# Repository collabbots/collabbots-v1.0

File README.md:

# collabbots-v1.0

Pictures of the setup (July 2019):

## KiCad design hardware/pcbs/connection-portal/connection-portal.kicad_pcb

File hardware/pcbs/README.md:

**Lessons learned**

Possible improvements for v2.0/v1.0 Rev B of the pcbs:

1. Reverse voltage protection using power PMOS, [zener, resistor (and LED for indication)]. **(vv important)**
2. integration of PCA9685 circuit into the pcb itself: reduce form factor and external wiring. **(vv important)**
3. For the connection portal pcb: the interrupt wires have to currently be all powered through one I-High and GND port. Rather have an array of 3 jumpers: interrupt, power, GND so that it is easier to wire and manage micro/limit switches. **(important)**
4. Use bigger (appropriately sized) vias -- comparable to the track thickness
5. Make the LED circuits brighter -- use transistors
6. Make an enclosure for the pcbs, with place for the knobs to come out.
7. Properly label all connections and components on the pcb (both sides for clarity and ease of use)
8. The number of motors is 4, but the connection portal and controller have capacity and connections for 5. This is a mismatch; keep the limit of motors to 4 if the arm design remains the same.
9. Have a port for the switch, which will interrupt the input power. This can be done by having a mount for a fuse between the switch and input power, so that traces don't have to be very thick and instead GND can go through the fuse from the switch. **(vv important)**
10. Have a dedicated place to mount the buck converter output fuse on the controller which could be a thick screw terminal, maybe. **(important)** 
11. The V+ and GND plates act like a capacitor and is dangerous for sensitive equipment or devices monitoring V+ since even after cutting the supply, V+ is floating at 1.5V or higher. Design circuitry to discharge this without overloading the supply and overheating when switched on. **(important)**
12. Arrange the terminal block for the two arms so that it is easier to wire them. one on left and the other on right.
13. Can mount the RPi on the bottom, thereby reducing the PCB footprint by a lot, and also allowing enough space for routing cables for the RPi.
14. Try using SMD components to further reduce the footprint.
15. Can have LED indicators for all the wires for visual debugging and also. Use the on-board 5V supply for that.
16. Try redesigning the pcb such that the design is completely modular. Another controller pcb can add two more arms at maximum. Therefore removing RPi from the board and having it has an optional mount is one step towards achieving this. **(vvv important)**
17. Servo zero set correction circuitry (try adding large capacitors on the output -- make sure to avoid high current surges). **(vv important)**
18. The connection portal will not be necessary if we handle each robot using a small microcontroller. This will also enable parallel control. So, just a USB cable and power supply goes into the robot -- also reduces wiring tremendously.
19. There can be a USB interface board that handles distributing serial commands to multiple robots. So, from a single USB port of the RPi/computer, you have a command handler PCB connected to multiple robots through USB ports. This will promote expandibility of the system.

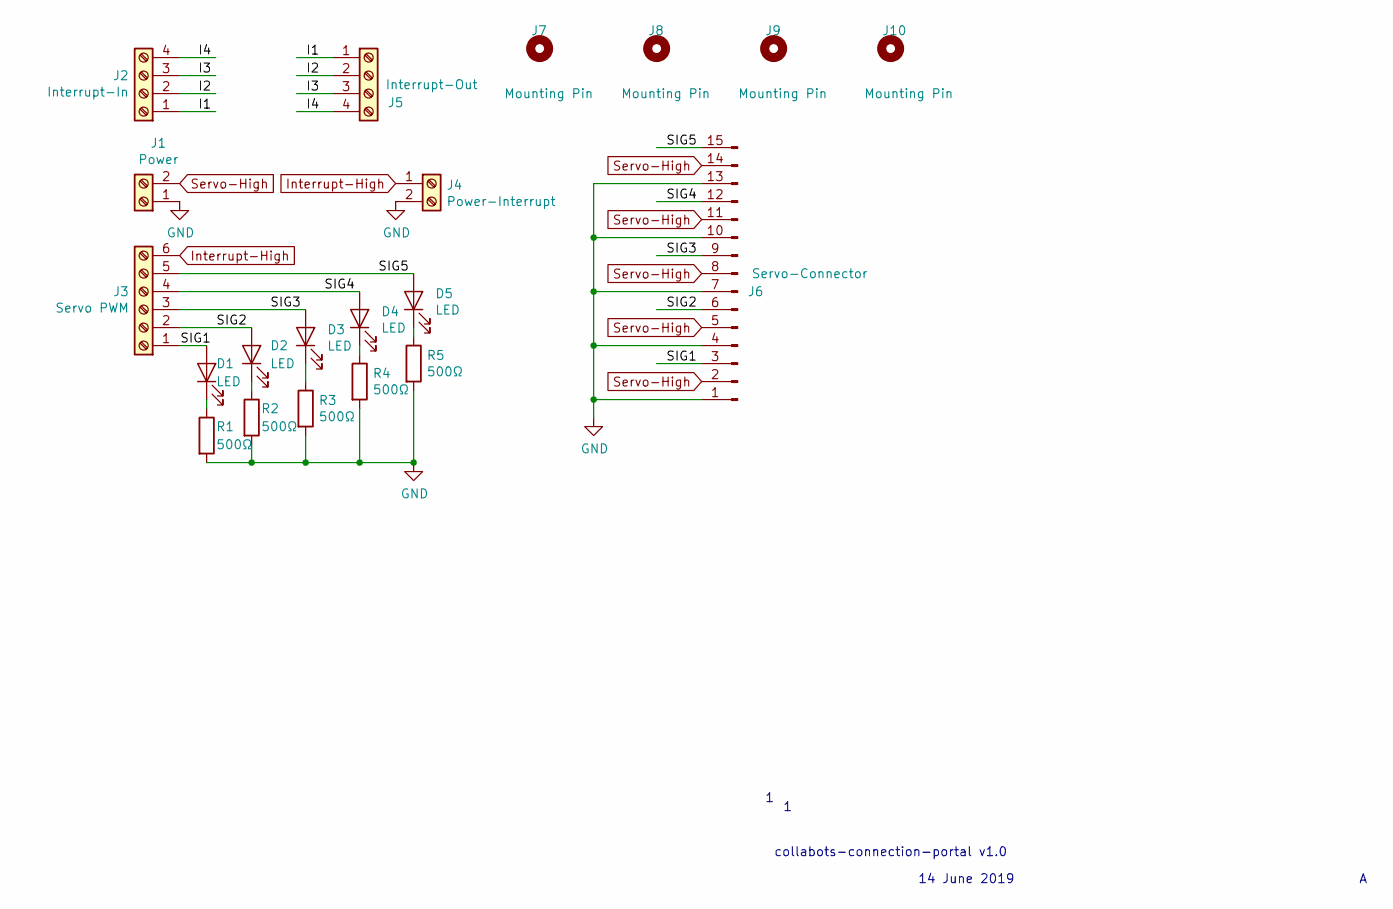
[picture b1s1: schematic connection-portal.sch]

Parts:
D1, D2, D3, D4, D5: LED; LED_Rectangular_W3.9mm_H1.8mm_FlatTop
J1: Power; TerminalBlock_MetzConnect_Type011_RT05502HBWC_1x02_P5.00mm_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
J2: Interrupt-In; TerminalBlock_MetzConnect_Type011_RT05504HBWC_1x04_P5.00mm_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
J3: Servo PWM; TerminalBlock_MetzConnect_Type011_RT05506HBWC_1x06_P5.00mm_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
J4: Power-Interrupt; TerminalBlock_MetzConnect_Type011_RT05502HBWC_1x02_P5.00mm_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
J5: Interrupt-Out; TerminalBlock_MetzConnect_Type011_RT05504HBWC_1x04_P5.00mm_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
J6: Servo-Connector; PinHeader_1x15_P2.54mm_Horizontal
J7, J8, J9, J10: Mounting Pin; MountingHole_3.2mm_M3
R1, R2, R3, R4, R5: 500Ω; R_Axial_DIN0207_L6.3mm_D2.5mm_P10.16mm_Horizontal

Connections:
/I1: J2.1, J5.1
/I2: J2.2, J5.2
/I3: J2.3, J5.3
/I4: J2.4, J5.4
/SIG1: D1.2 (A), J3.1, J6.3
/SIG2: D2.2 (A), J3.2, J6.6
/SIG3: D3.2 (A), J3.3, J6.9
/SIG4: D4.2 (A), J3.4, J6.12
/SIG5: D5.2 (A), J3.5, J6.15
GND: J1.1, J4.2, J6.1, J6.4, J6.7, J6.10, J6.13, R1.2, R2.2, R3.2, R4.2, R5.2
Interrupt-High: J3.6, J4.1
unnamed: D1.1 (K), R1.1
unnamed: D2.1 (K), R2.1
unnamed: D3.1 (K), R3.1
unnamed: D4.1 (K), R4.1
unnamed: D5.1 (K), R5.1
Servo-High: J1.2, J6.2, J6.5, J6.8, J6.11, J6.14

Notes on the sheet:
collabots-connection-portal v1.0
14 June 2019

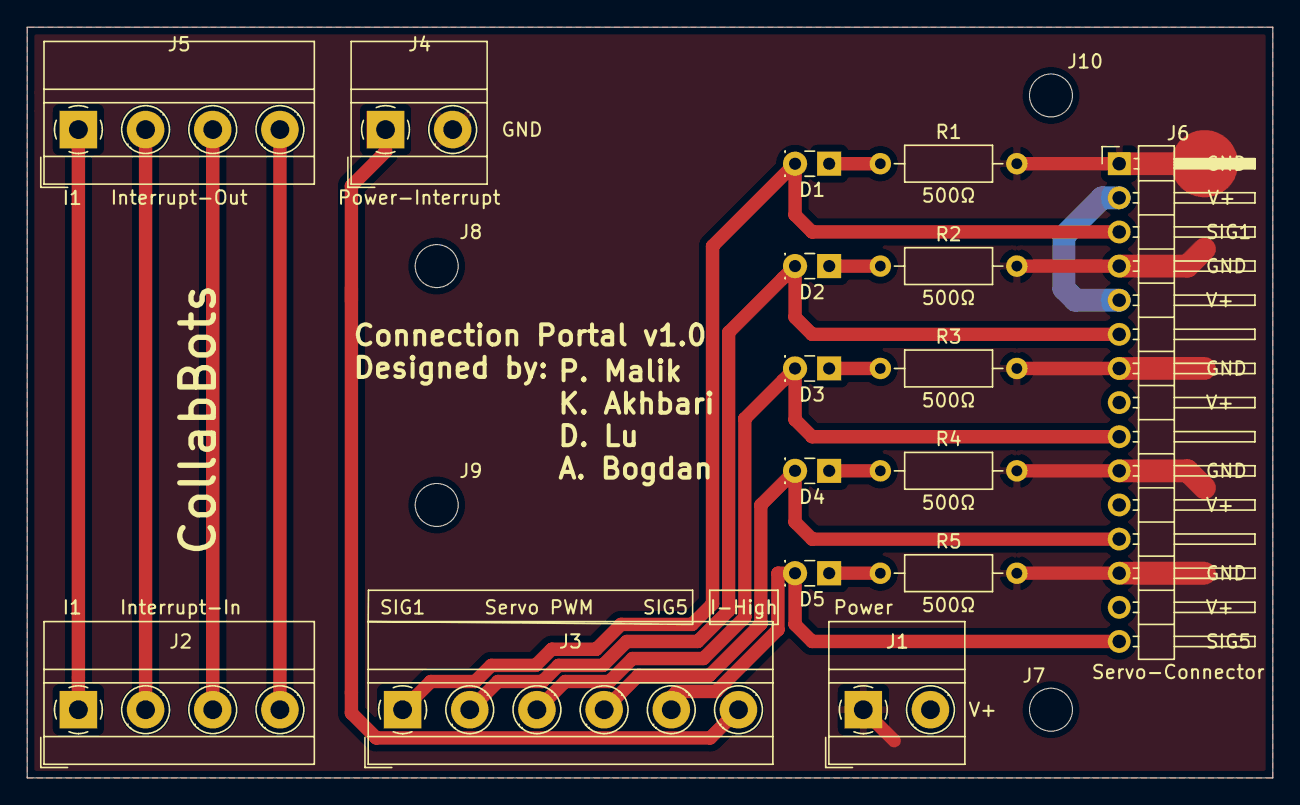
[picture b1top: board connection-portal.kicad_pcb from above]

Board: 2 copper layers, 92.7 x 55.9 mm, 20 parts (0 on the bottom side), 17 nets.

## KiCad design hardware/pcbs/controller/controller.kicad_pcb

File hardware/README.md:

# hardware
Wiring diagrams, PCBs, and CAD files for the robots' hardware

**Controller PCB**

**Connection Portal PCB**

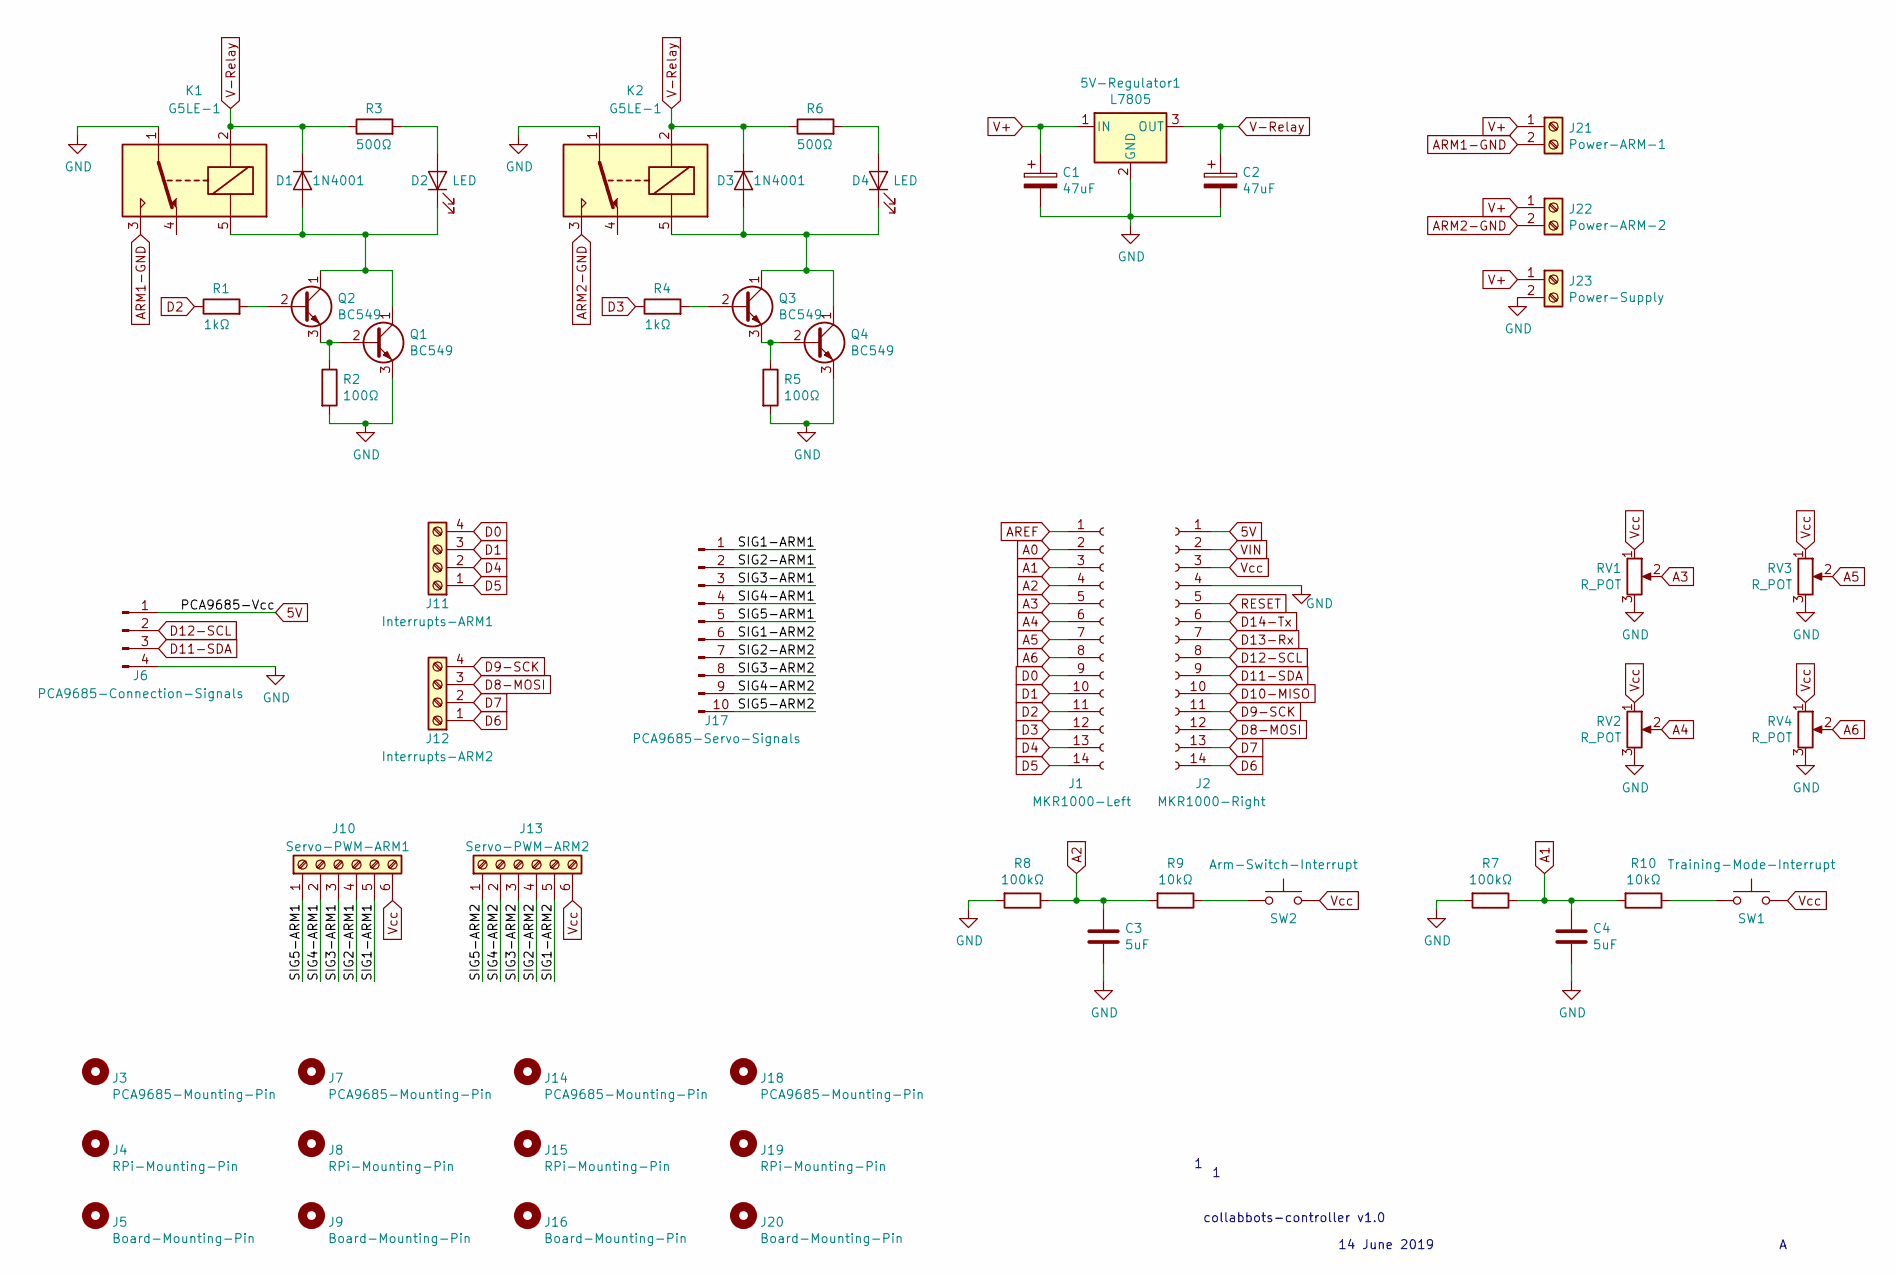
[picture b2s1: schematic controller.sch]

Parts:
5V-Regulator1: L7805; TO-220F-3_Vertical
C1, C2: 47uF; CP_Radial_D4.0mm_P1.50mm
C3: 5uF; C_Disc_D3.0mm_W1.6mm_P2.50mm
C4: 5uF
D1, D3: 1N4001; D_DO-41_SOD81_P10.16mm_Horizontal
D2, D4: LED; LED_Rectangular_W3.9mm_H1.8mm_FlatTop
J1: MKR1000-Left; PinHeader_1x14_P2.54mm_Vertical
J2: MKR1000-Right; PinHeader_1x14_P2.54mm_Vertical
J3, J7, J14, J18: PCA9685-Mounting-Pin; MountingHole_2.2mm_M2
J4, J8, J15, J19: RPi-Mounting-Pin; MountingHole_2.2mm_M2
J5, J9, J16, J20: Board-Mounting-Pin; MountingHole_3.2mm_M3
J6: PCA9685-Connection-Signals; PinHeader_1x04_P2.54mm_Vertical
J10: Servo-PWM-ARM1; TerminalBlock_MetzConnect_Type011_RT05506HBWC_1x06_P5.00mm_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
J11: Interrupts-ARM1; TerminalBlock_MetzConnect_Type011_RT05504HBWC_1x04_P5.00mm_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
J12: Interrupts-ARM2; TerminalBlock_MetzConnect_Type011_RT05504HBWC_1x04_P5.00mm_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
J13: Servo-PWM-ARM2; TerminalBlock_MetzConnect_Type011_RT05506HBWC_1x06_P5.00mm_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
J17: PCA9685-Servo-Signals; PinHeader_1x10_P2.54mm_Vertical
J21: Power-ARM-1; TerminalBlock_MetzConnect_Type011_RT05502HBWC_1x02_P5.00mm_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
J22: Power-ARM-2; TerminalBlock_MetzConnect_Type011_RT05502HBWC_1x02_P5.00mm_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
J23: Power-Supply; TerminalBlock_MetzConnect_Type011_RT05502HBWC_1x02_P5.00mm_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
K1, K2: G5LE-1; Relay_SPDT_Omron-G5LE-1
Q1, Q2, Q3, Q4: BC549; TO-92_Inline
R1, R4: 1kΩ; R_Axial_DIN0207_L6.3mm_D2.5mm_P10.16mm_Horizontal
R2, R5: 100Ω; R_Axial_DIN0207_L6.3mm_D2.5mm_P10.16mm_Horizontal
R3, R6: 500Ω; R_Axial_DIN0207_L6.3mm_D2.5mm_P10.16mm_Horizontal
R7, R8: 100kΩ; R_Axial_DIN0207_L6.3mm_D2.5mm_P10.16mm_Horizontal
R9, R10: 10kΩ; R_Axial_DIN0207_L6.3mm_D2.5mm_P10.16mm_Horizontal
RV1, RV2, RV3, RV4: R_POT; Potentiometer_Alps_RK163_Single_Horizontal
SW1: Training-Mode-Interrupt; SW_Tactile_Straight_KSL0Axx1LFTR
SW2: Arm-Switch-Interrupt; SW_Tactile_Straight_KSL0Axx1LFTR

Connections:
5V: J2.1, J6.1
/SIG1-ARM1: J10.5, J17.1
/SIG1-ARM2: J13.5, J17.6
/SIG2-ARM1: J10.4, J17.2
/SIG2-ARM2: J13.4, J17.7
/SIG3-ARM1: J10.3, J17.3
/SIG3-ARM2: J13.3, J17.8
/SIG4-ARM1: J10.2, J17.4
/SIG4-ARM2: J13.2, J17.9
/SIG5-ARM1: J10.1, J17.5
/SIG5-ARM2: J13.1, J17.10
A0: J1.2
A1: C4.1, J1.3, R7.1, R10.2
A2: C3.1, J1.4, R8.1, R9.2
A3: J1.5, RV1.2
A4: J1.6, RV2.2
A5: J1.7, RV3.2
A6: J1.8, RV4.2
AREF: J1.1
ARM1-GND: J21.2, K1.3
ARM2-GND: J22.2, K2.3
D0: J1.9, J11.4
D1: J1.10, J11.3
D2: J1.11, R1.1
D3: J1.12, R4.1
D4: J1.13, J11.2
D5: J1.14, J11.1
D6: J2.14, J12.1
D7: J2.13, J12.2
D8-MOSI: J2.12, J12.3
D9-SCK: J2.11, J12.4
D10-MISO: J2.10
D11-SDA: J2.9, J6.3
D12-SCL: J2.8, J6.2
D13-Rx: J2.7
D14-Tx: J2.6
GND: 5V-Regulator1.2 (GND), C1.2, C2.2, C3.2, C4.2, J2.4, J6.4, J23.2, K1.1, K2.1, Q1.3 (E), Q4.3 (E), R2.2, R5.2, R7.2, R8.2, RV1.3, RV2.3, RV3.3, RV4.3
unnamed: D1.2 (A), D2.1 (K), K1.5, Q1.1 (C), Q2.1 (C)
unnamed: D2.2 (A), R3.2
unnamed: D3.2 (A), D4.1 (K), K2.5, Q3.1 (C), Q4.1 (C)
unnamed: D4.2 (A), R6.2
unnamed: Q1.2 (B), Q2.3 (E), R2.1
unnamed: Q2.2 (B), R1.2
unnamed: Q3.2 (B), R4.2
unnamed: Q3.3 (E), Q4.2 (B), R5.1
unnamed: R9.1, SW2.1
unnamed: R10.1, SW1.1
RESET: J2.5
V+: 5V-Regulator1.1 (IN), C1.1, J21.1, J22.1, J23.1
V-Relay: 5V-Regulator1.3 (OUT), C2.1, D1.1 (K), D3.1 (K), K1.2, K2.2, R3.1, R6.1
VIN: J2.2
Vcc: J2.3, J10.6, J13.6, RV1.1, RV2.1, RV3.1, RV4.1, SW1.2, SW2.2

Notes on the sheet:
collabbots-controller v1.0
14 June 2019

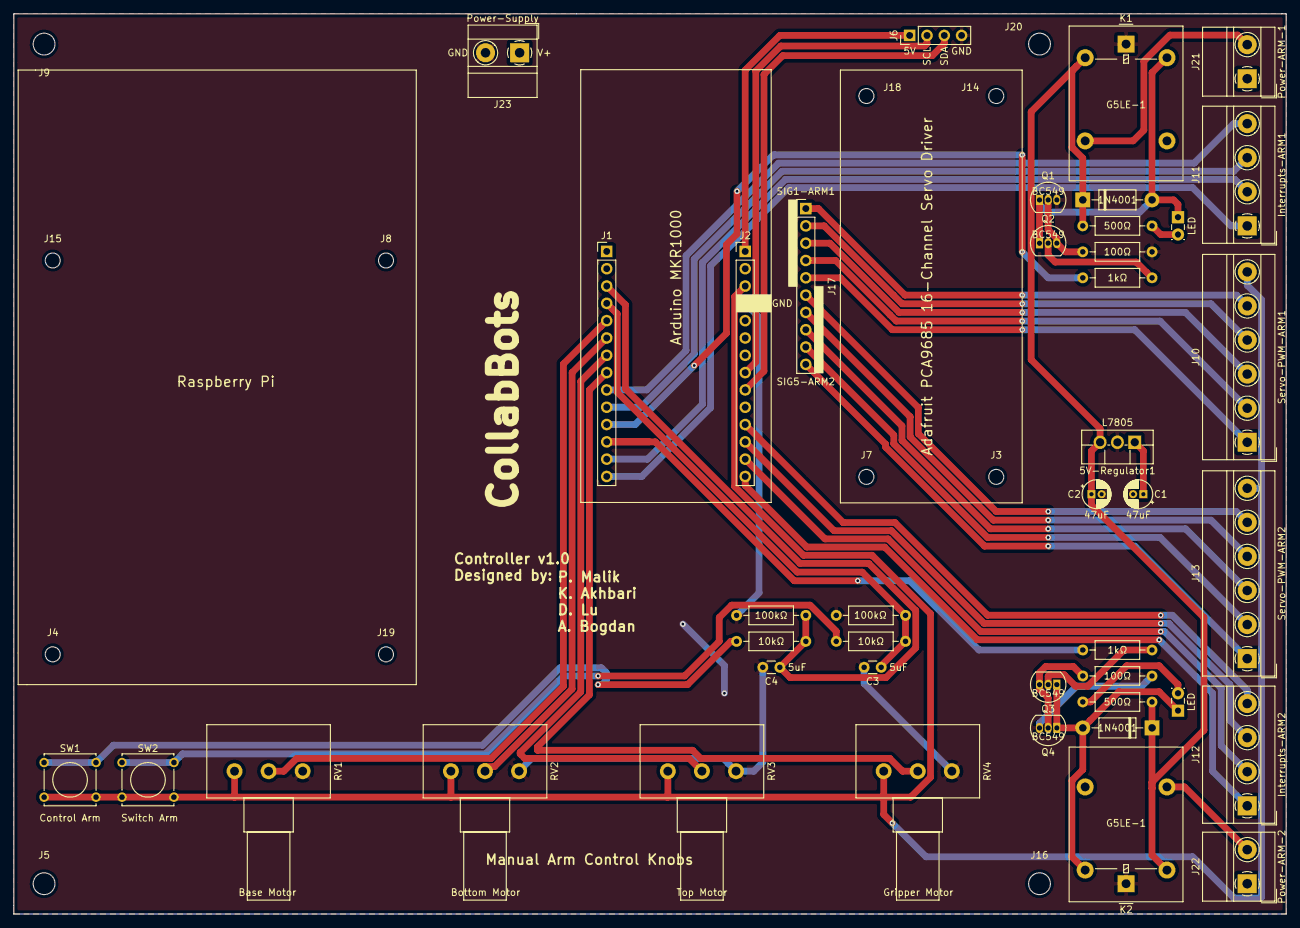
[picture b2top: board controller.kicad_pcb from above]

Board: 2 copper layers, 186.7 x 132.1 mm, 54 parts (0 on the bottom side), 45 nets.

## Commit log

2019-07-27 making a single repository to hold all sub-components
2019-07-28 programmed serial input (can type to manually move arm)
2019-07-28 can now use keyboard input to control the robot
2019-07-28 made the interface more user-friendly with feedback on what the arm is doing
2019-07-28 interrupts now work!
2019-07-29 added feedback on pcbs for future improvement
2019-07-29 added images
2019-07-29 fixed images
2019-07-29 removing unecessary files
2019-07-29 reorganizing driver. also need to expand for manual control and wireless state data transfer
2019-08-02 dividing driver into multiple files to manage complexity
2019-08-03 successfully divided code into multiple files
2019-08-03 added two modes through which the robot can be operated, and comments explaining how each one works (also coded on my own computer finally :))
2019-08-03 Pushing code to control arms w keyboard
2019-08-03 no message
2019-08-03 redo of previous commit to correct update errors
2019-08-03 added comments describing how the two modes work
2019-08-04 configured interrupts to configure mode
2019-08-04 new cpp file to send input to the arduino
2019-08-09 removing unwanted files. added gitignore
2019-08-09 removed build files from being tracked
2019-08-11 PS4 interface to control robot fully completed
2019-08-11 introduced new way to switch between modes; changed and improved PS4 control to make it more ergonomic; enabled turning off relay wirelessly
2019-08-18 Pushing vision code - Camera and Filters
2019-08-18 fully implemented colour filtering in a new Vision class
2019-08-18 new file: CMakeLists.txt
2019-08-19 added test functions for calibration
2019-10-16 added setup images
2019-10-16 showing setup
2020-03-21 Add Codacy badge
